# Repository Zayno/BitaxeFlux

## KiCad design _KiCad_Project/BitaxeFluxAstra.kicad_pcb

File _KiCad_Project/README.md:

# BitaxeFluxAstra A1 — Clean Engineering Project

Open `BitaxeFluxAstra.kicad_pro` in **KiCad 10**. All five editable sheets, the preserved board and all used symbol/footprint libraries are included.

This package is for **pre-layout engineering review**. The PCB remains the earlier snapshot; it does not implement all A1 schematic changes. Do not manufacture this board from this package or automatically update it from the schematic as part of cleanup.

The ASIC is **Bitmain BM1373**, reference **A1**, configuration **Mode 1**. Its local symbol is `BitaxeFluxAstra:BM1373_mode1` and its footprint is `BitaxeFluxAstra:BM1373`.

R49 remains DNP. Unqualified thermal-shutdown and optional programming/tuning parts retain their DNP states. Qualification HOLD items remain open.

Read `PROJECT_CLEANUP_REPORT.md` for verification, preserved HOLD items and limitations. Exact historical file/migration names are isolated in `engineering_reference_notes.md`. `BitaxeFluxAstra_Integrity.json` records current structural verification. `SHA256SUMS.txt` covers delivery files except itself.

Static equivalence and extracted-package dependency checks passed. **Native KiCad opening, ERC, DRC and exported-netlist comparison have not been run** in this environment. Full acceptance remains pending that review. Optional standard 3D models use the normal KiCad 10 3D-model package; every required custom model is local or embedded.

No placement, routing or fabrication outputs are included. The supplied licence is preserved in `LICENSE`.

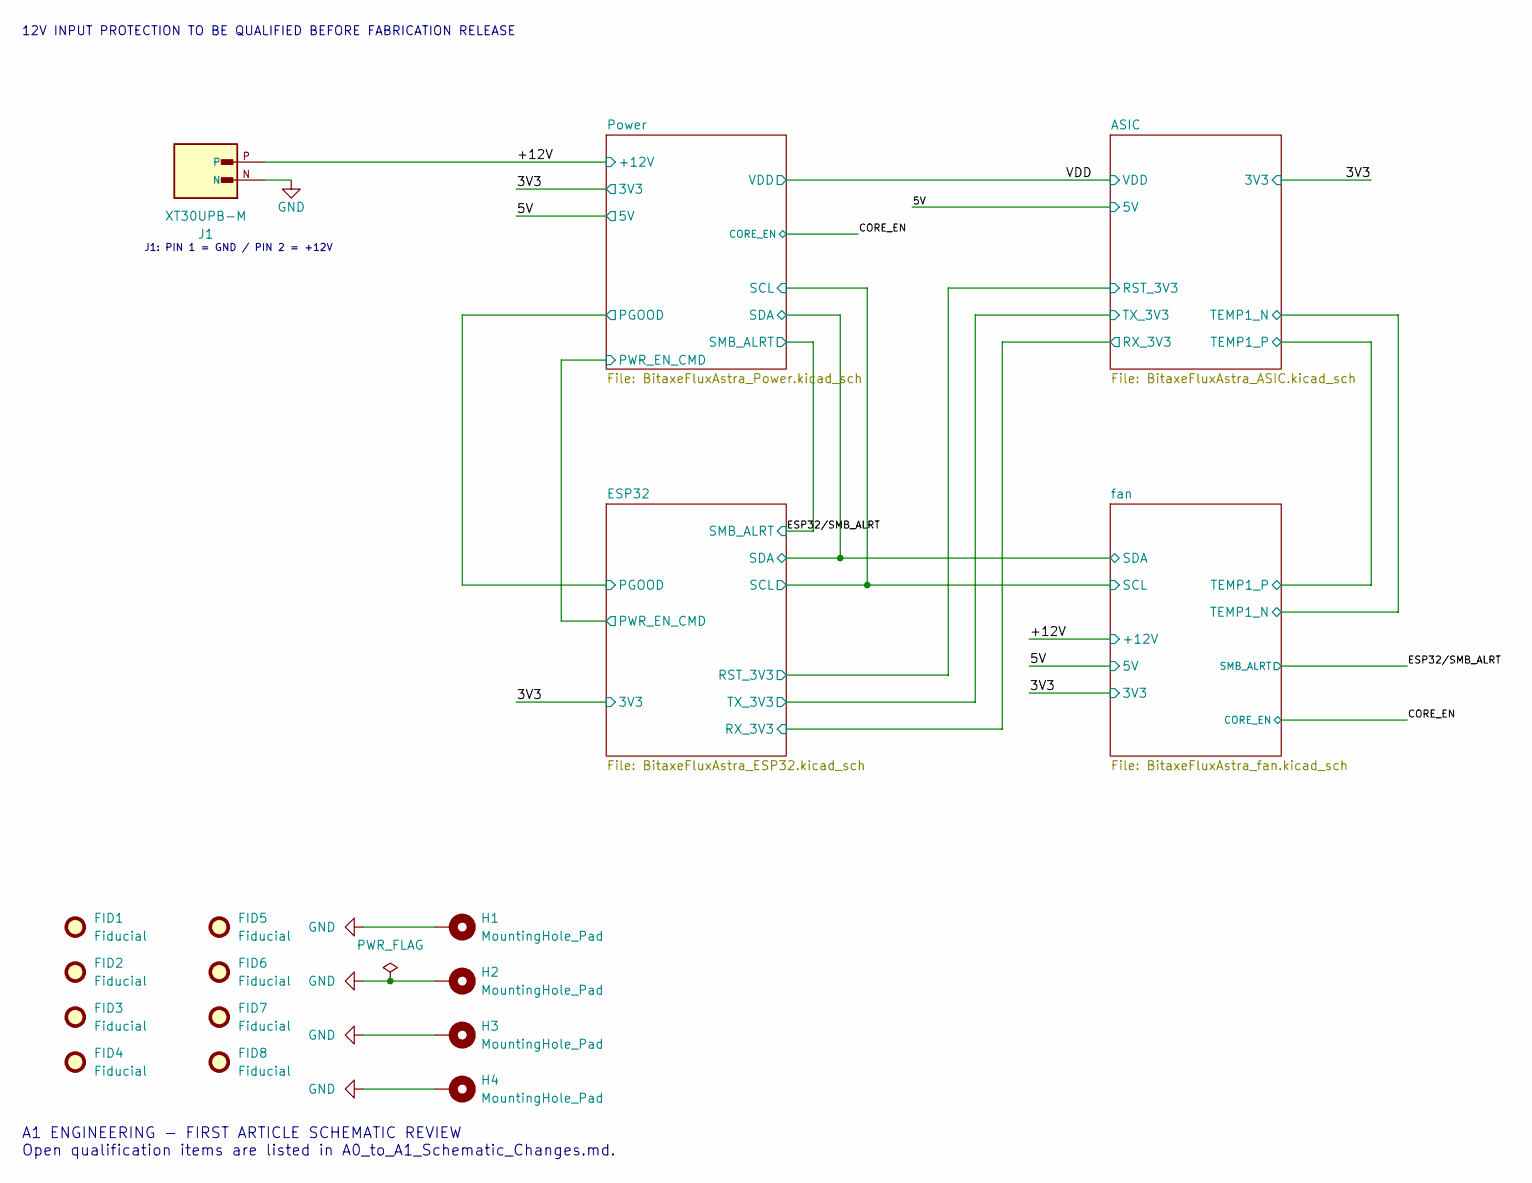
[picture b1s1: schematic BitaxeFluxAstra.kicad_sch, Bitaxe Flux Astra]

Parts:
FID1, FID2, FID3, FID4, FID5, FID6, FID7, FID8: Fiducial; Fiducial_1mm_Mask2mm
H1, H2, H3, H4: MountingHole_Pad; MountingHole_3.2mm_M3_Pad_Via
J1: XT30UPB-M; AMASS_XT30UPB-M

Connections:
+12V: J1.P; also elsewhere on the board
GND: H1.1 (1_1), H2.1 (1_1), H3.1 (1_1), H4.1 (1_1), J1.N; also elsewhere on the board

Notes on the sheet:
J1: PIN 1 = GND / PIN 2 = +12V
A1 ENGINEERING - FIRST ARTICLE SCHEMATIC REVIEW Open qualification items are listed in A0_to_A1_Schematic_Changes.md.
12V INPUT PROTECTION TO BE QUALIFIED BEFORE FABRICATION RELEASE

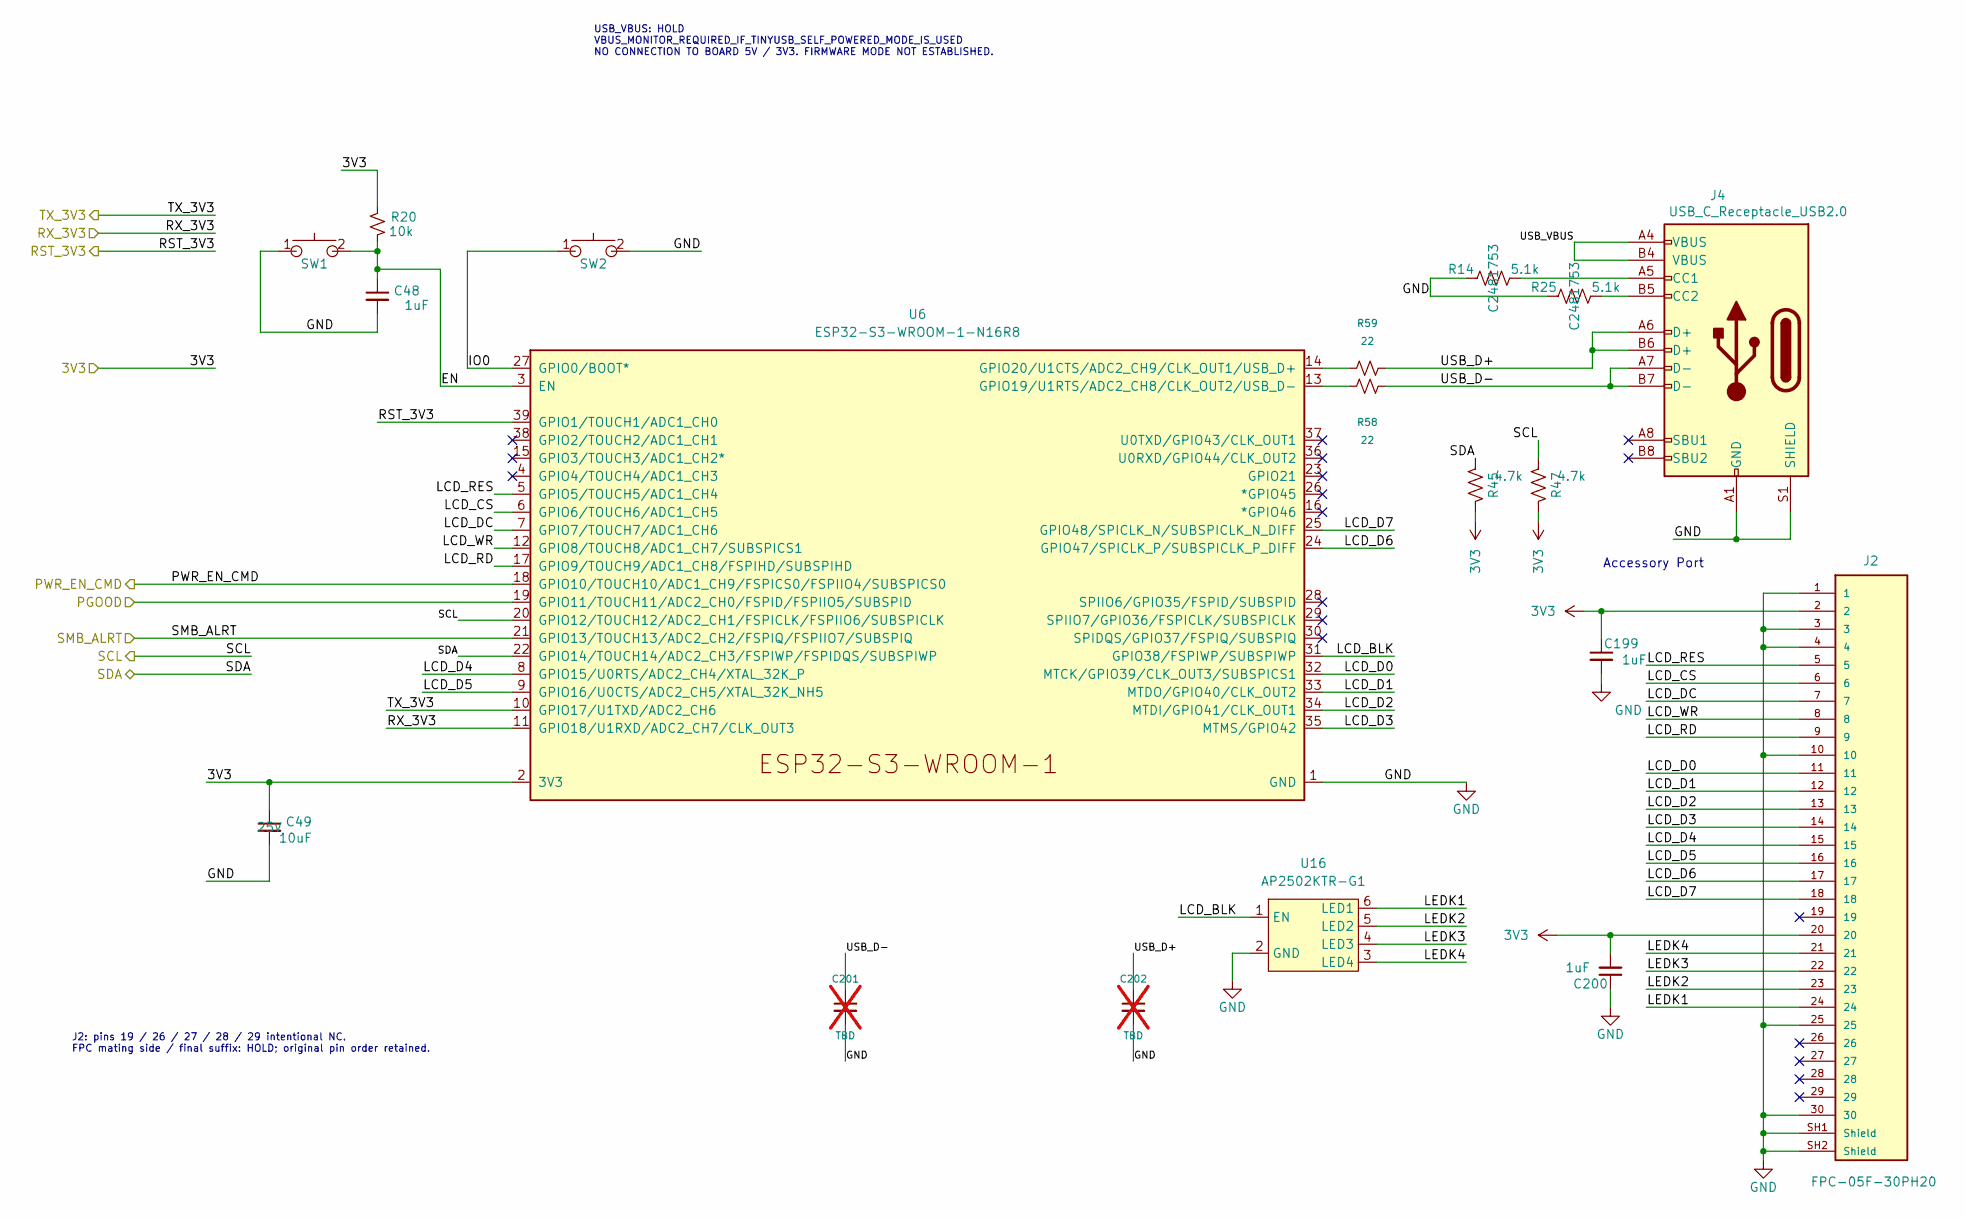
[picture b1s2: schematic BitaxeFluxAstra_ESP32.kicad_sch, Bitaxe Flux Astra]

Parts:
C48, C199, C200: 1uF; C_0603_1608Metric; PARTNO TMK107B7105KA-T
C49: 10uF; C_0603_1608Metric; Voltage 25V; PARTNO GRM188R61E106KA73D; LCSC C344022
C201, C202: TBD; C_0402_1005Metric; PARTNO TBD / QUALIFY; not fitted
J2: FPC-05F-30PH20; FPC-SMD_30P-P0.50_XUNPU_FPC-05F-30PH20; PARTNO FPC-05FB-30PH20
J4: USB_C_Receptacle_USB2.0; USB_C_Receptacle_GCT_USB4105-xx-A; PARTNO USB4105-GF-A
R14, R25: 5.1k; R_0402_1005Metric; PARTNO RMCF0402JT5K10; LCSC C2481753
R20: 10k; R_0402_1005Metric; PARTNO RC0402JR-0710KL; LCSC C25744
R45, R47: 4.7k; R_0402_1005Metric; PARTNO RC0402DR-074K7L; LCSC C471788
R58, R59: 22; R_0402_1005Metric; PARTNO RC0402FR-0722RL
SW1, SW2: SW_Push_SPST_NO; SW_CS1213AGF260_CRS; PARTNO CS1213AGF260
U6: ESP32-S3-WROOM-1-N16R8; ESP32-S3-WROOM-1; PARTNO ESP32-S3-WROOM-1-N16R8
U16: AP2502KTR-G1; SOT-23-6; PARTNO AP2502KTR-G1

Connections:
3V3: C49.1, C199.1, C200.2, J2.2, J2.20, R20.2, R45.1, R47.1, U6.2 (3V3); also elsewhere on the board
/ASIC/RST_3V3: U6.39 (GPIO1/TOUCH1/ADC1_CH0); also elsewhere on the board
/ASIC/RX_3V3: U6.11 (GPIO18/U1RXD/ADC2_CH7/CLK_OUT3); also elsewhere on the board
/ASIC/TX_3V3: U6.10 (GPIO17/U1TXD/ADC2_CH6); also elsewhere on the board
/ESP32/EN: C48.1, R20.1, SW1.2, U6.3 (EN)
/ESP32/IO0: SW2.1, U6.27 (GPIO0/BOOT*)
/ESP32/LCD_BLK: U6.31 (GPIO38/FSPIWP/SUBSPIWP), U16.1 (EN)
/ESP32/LCD_CS: J2.6, U6.6 (GPIO6/TOUCH6/ADC1_CH5)
/ESP32/LCD_D0: J2.11, U6.32 (MTCK/GPIO39/CLK_OUT3/SUBSPICS1)
/ESP32/LCD_D1: J2.12, U6.33 (MTDO/GPIO40/CLK_OUT2)
/ESP32/LCD_D2: J2.13, U6.34 (MTDI/GPIO41/CLK_OUT1)
/ESP32/LCD_D3: J2.14, U6.35 (MTMS/GPIO42)
/ESP32/LCD_D4: J2.15, U6.8 (GPIO15/U0RTS/ADC2_CH4/XTAL_32K_P)
/ESP32/LCD_D5: J2.16, U6.9 (GPIO16/U0CTS/ADC2_CH5/XTAL_32K_NH5)
/ESP32/LCD_D6: J2.17, U6.24 (GPIO47/SPICLK_P/SUBSPICLK_P_DIFF)
/ESP32/LCD_D7: J2.18, U6.25 (GPIO48/SPICLK_N/SUBSPICLK_N_DIFF)
/ESP32/LCD_DC: J2.7, U6.7 (GPIO7/TOUCH7/ADC1_CH6)
/ESP32/LCD_RD: J2.9, U6.17 (GPIO9/TOUCH9/ADC1_CH8/FSPIHD/SUBSPIHD)
/ESP32/LCD_RES: J2.5, U6.5 (GPIO5/TOUCH5/ADC1_CH4)
/ESP32/LCD_WR: J2.8, U6.12 (GPIO8/TOUCH8/ADC1_CH7/SUBSPICS1)
/ESP32/LEDK1: J2.24, U16.6 (LED1)
/ESP32/LEDK2: J2.23, U16.5 (LED2)
/ESP32/LEDK3: J2.22, U16.4 (LED3)
/ESP32/LEDK4: J2.21, U16.3 (LED4)
/ESP32/PWR_EN_CMD: U6.18 (GPIO10/TOUCH10/ADC1_CH9/FSPICS0/FSPIIO4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); also elsewhere on the board
/ESP32/SCL: R47.2, U6.20 (GPIO12/TOUCH12/ADC2_CH1/FSPICLK/FSPIIO6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); also elsewhere on the board
/ESP32/SDA: R45.2, U6.22 (GPIO14/TOUCH14/ADC2_CH3/FSPIWP/FSPIDQS/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); also elsewhere on the board
/ESP32/USB_D+: C202.1, J4.A6 (D+), J4.B6 (D+), R59.2
/ESP32/USB_D-: C201.1, J4.A7 (D-), J4.B7 (D-), R58.2
/ESP32/USB_VBUS: J4.A4 (VBUS), J4.B4 (VBUS)
/ESP32/SMB_ALRT: U6.21 (GPIO13/TOUCH13/ADC2_CH2/FSPIQ/FSPIIO7/S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); also elsewhere on the board
/Power/PGOOD: U6.19 (GPIO11/TOUCH11/ADC2_CH0/FSPID/FSPIIO5/S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); also elsewhere on the board
GND: C48.2, C49.2, C199.2, C200.1, C201.2, C202.2, J2.1, J2.3, J2.4, J2.10, J2.25, J2.30, J2.SH1 (Shield), J2.SH2 (Shield), J4.A1 (GND), J4.B1 (GND), J4.S1 (SHIELD), R14.1, R25.1, SW1.1, SW2.2, U6.1 (GND), U6.40 (GND), U6.41 (GND), U16.2 (GND); also elsewhere on the board
unnamed: J4.A5 (CC1), R14.2
unnamed: J4.B5 (CC2), R25.2
unnamed: R58.1, U6.13 (GPIO19/U1RTS/ADC2_CH8/CLK_OUT2/USB_D-)
unnamed: R59.1, U6.14 (GPIO20/U1CTS/ADC2_CH9/CLK_OUT1/USB_D+)

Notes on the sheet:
J2: pins 19 / 26 / 27 / 28 / 29 intentional NC. FPC mating side / final suffix: HOLD; original pin order retained.
USB_VBUS: HOLD VBUS_MONITOR_REQUIRED_IF_TINYUSB_SELF_POWERED_MODE_IS_USED NO CONNECTION TO BOARD 5V / 3V3. FIRMWARE MODE NOT ESTABLISHED.
Accessory Port

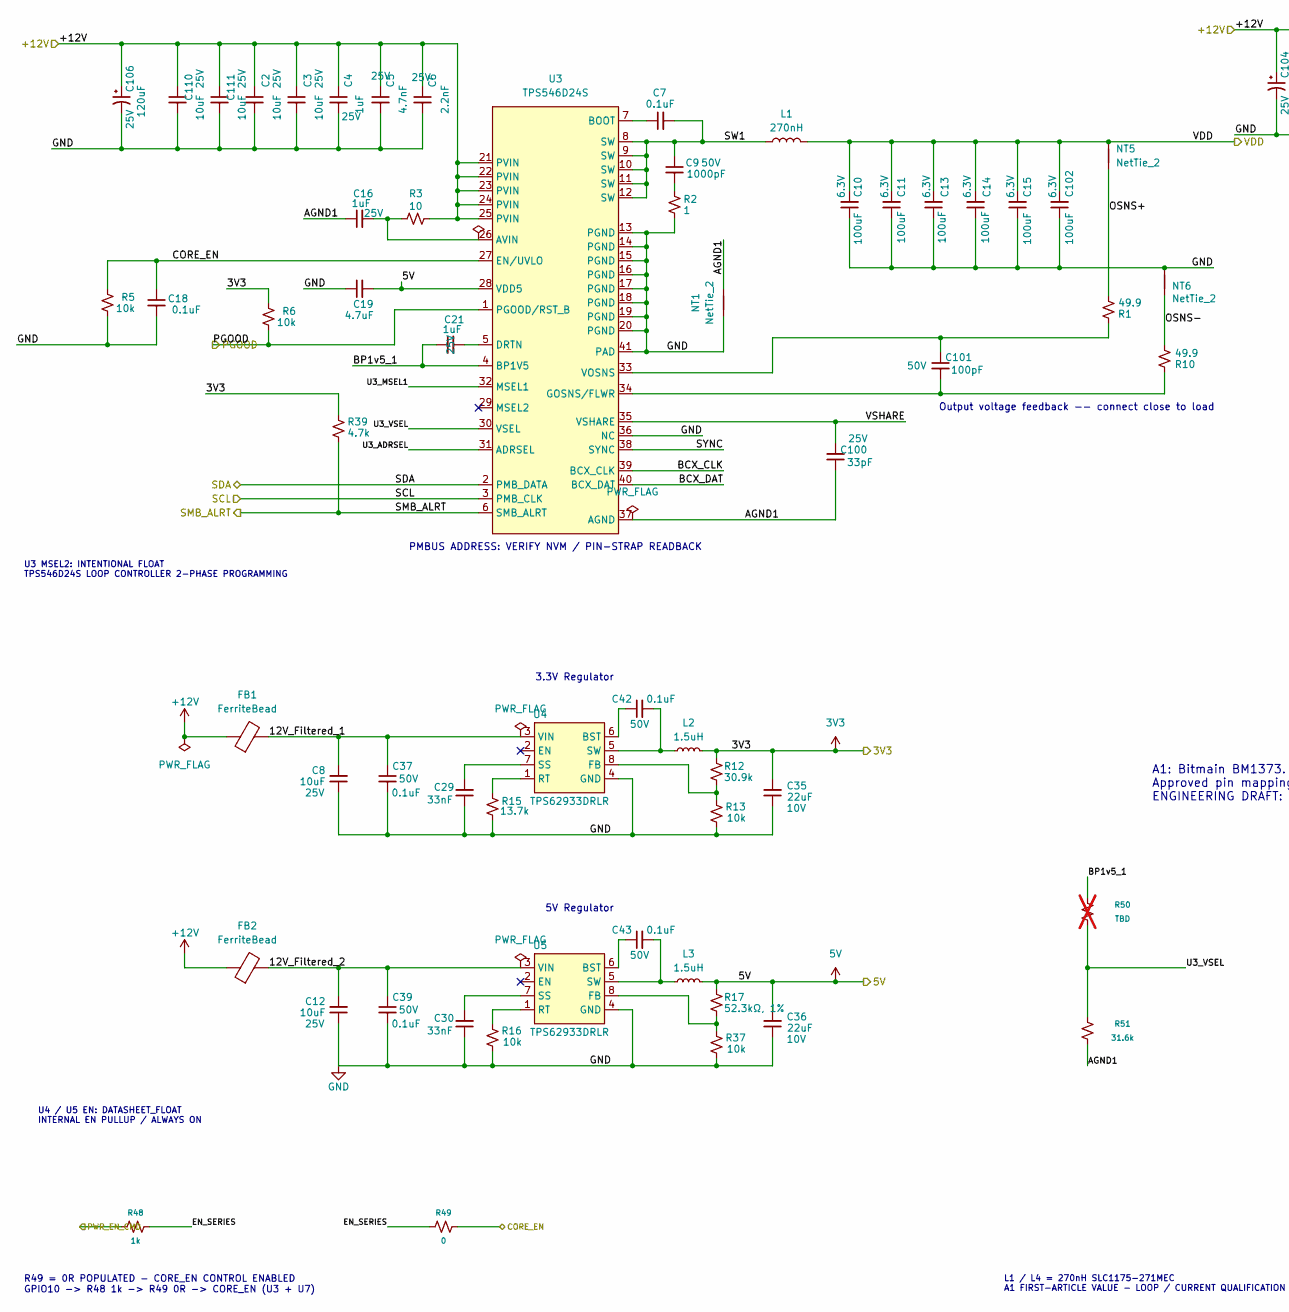
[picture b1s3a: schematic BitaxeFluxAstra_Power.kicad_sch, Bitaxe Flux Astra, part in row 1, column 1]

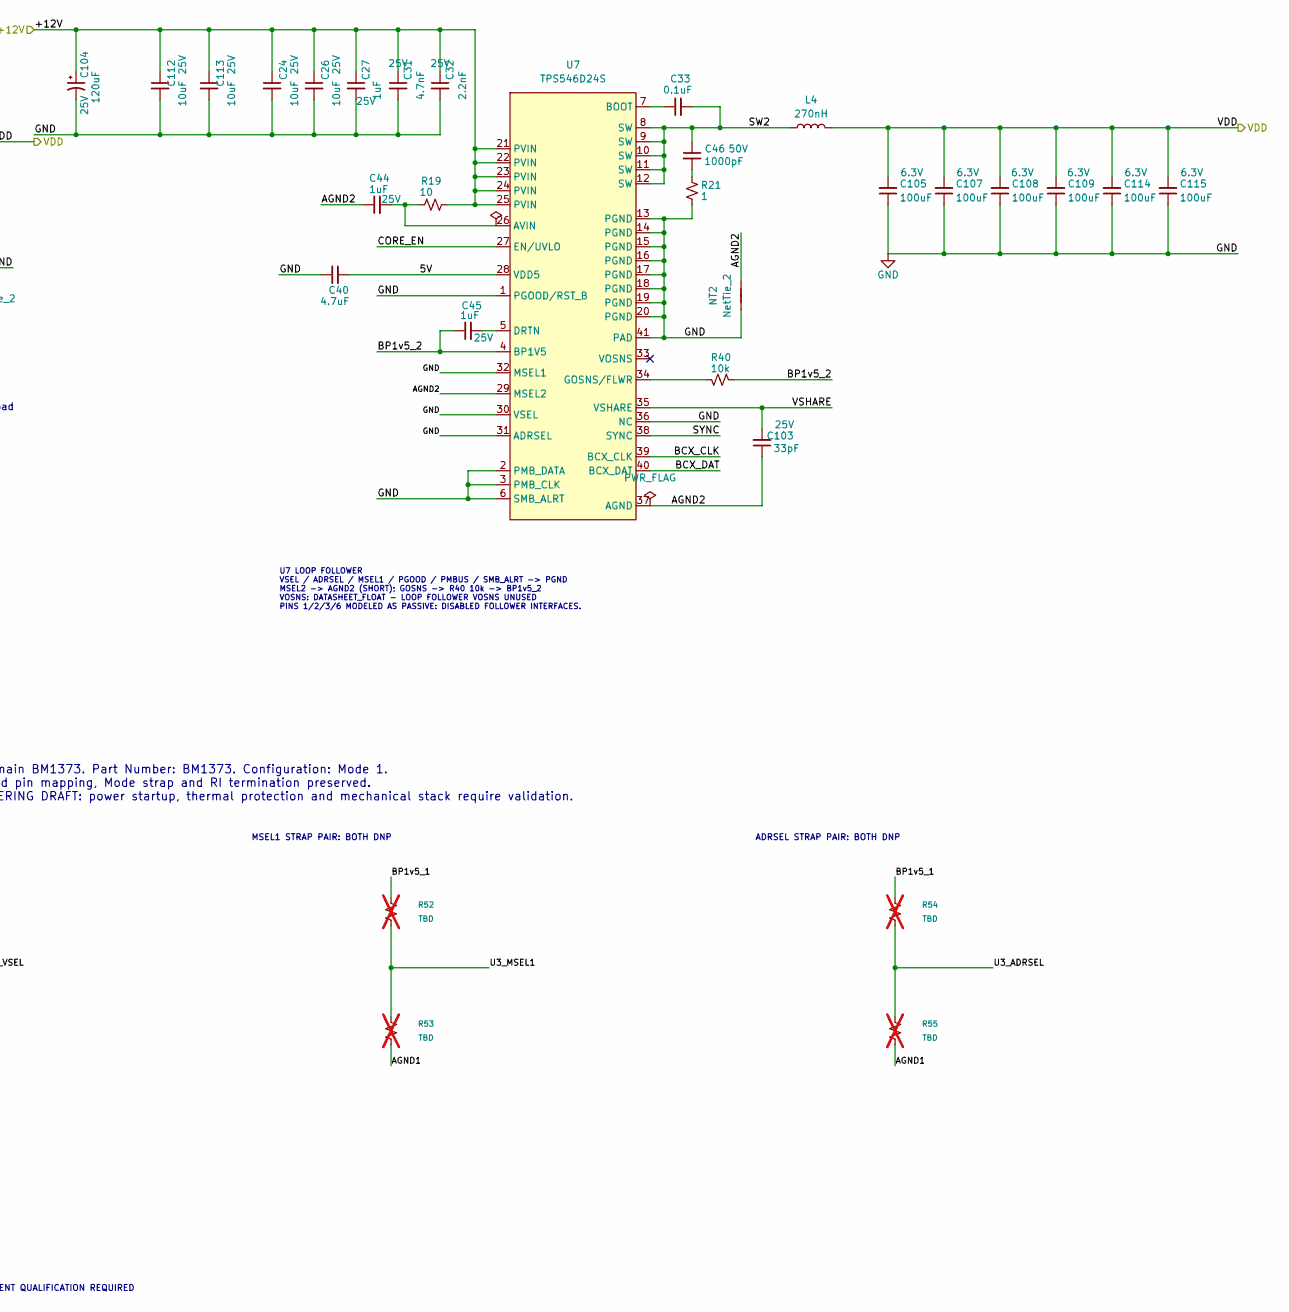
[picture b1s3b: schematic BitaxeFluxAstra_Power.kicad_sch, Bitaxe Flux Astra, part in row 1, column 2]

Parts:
C2, C3, C24, C26, C110, C111, C112, C113: 10uF; C_0603_1608Metric; Voltage 25V; PARTNO GRM188R61E106KA73D
C4, C16, C21, C27, C44, C45: 1uF; C_0603_1608Metric; Voltage 25V; PARTNO TMK107B7105KA-T
C5, C31: 4.7nF; C_0402_1005Metric; Voltage 25V; PARTNO GRM155R71E472KA01D
C6, C32: 2.2nF; C_0402_1005Metric; Voltage 25V; PARTNO GRM155R61H222KA01D
C7, C18, C33: 0.1uF; C_0402_1005Metric; PARTNO KGM05AR71C104KH
C8, C12: 10uF; C_0603_1608Metric; Voltage 25V; PARTNO GRM188R61E106KA73D; LCSC C344022
C9, C46: 1000pF; C_0805_2012Metric; Voltage 50V; PARTNO CC0805KRX7R9BB102
C10, C11, C13, C14, C15, C102, C105, C107, C108, C109, C114, C115: 100uF; C_1206_3216Metric; Voltage 6.3V; PARTNO CL31A107MQHNNNE
C19, C40: 4.7uF; C_0402_1005Metric; PARTNO GRM155R61A475MEAAD
C29, C30: 33nF; C_0402_1005Metric; PARTNO CC0402KRX7R9BB333; LCSC C106862
C35, C36: 22uF; C_0805_2012Metric; Voltage 10V; PARTNO CL21A226MPQNNNE; LCSC C29277
C37, C39, C42, C43: 0.1uF; C_0402_1005Metric; Voltage 50V; PARTNO GRM155R71H104KE14D; LCSC C77020
C100, C103: 33pF; C_0402_1005Metric; Voltage 25V; PARTNO KGM05ACG1E330JH
C101: 100pF; C_0402_1005Metric; Voltage 50V; PARTNO CC0402JRNPO9BN101
C104, C106: 120uF; CP_Elec_6.3x5.9; Voltage 25V; PARTNO TBD / QUALIFY
FB1, FB2: FerriteBead; C_1206_3216Metric; PARTNO BLM31KN601SN1L
L1, L4: 270nH; SLC1175-271MEC_COC; PARTNO SLC1175-271MEC
L2, L3: 1.5uH; IND-SMD_L2.0-W1.6; PARTNO FTC201612S1R5MBCA; LCSC C5832350
NT1, NT2, NT5, NT6: NetTie_2; NetTie-2_SMD_Pad0.2mmx1mm
R1, R10: 49.9; R_0402_1005Metric; PARTNO RC0402FR-0749R9L
R2, R21: 1; R_0805_2012Metric; PARTNO ESR10EZPJ1R0
R3, R19: 10; R_0402_1005Metric; PARTNO RC0402FR-0710RL
R5, R6, R40: 10k; R_0402_1005Metric; PARTNO RC0402JR-0710KL
R12: 30.9k; R_0402_1005Metric; PARTNO RC0402FR-0730K9L; LCSC C185428
R13, R16: 10k; R_0402_1005Metric; PARTNO RC0402JR-0710KL; LCSC C25744
R15: 13.7k; R_0402_1005Metric; PARTNO RC0402FR-0713K7L; LCSC C274888
R17: 52.3kΩ, 1%; R_0402_1005Metric
R37: 10k; R_0402_1005Metric
R39: 4.7k; R_0402_1005Metric; PARTNO RC0402JR-074K7L
R48: 1k; R_0402_1005Metric; PARTNO RC0402FR-071KL
R49: 0; R_0402_1005Metric; PARTNO Yageo RC0402JR-070RL
R50, R52, R53, R54, R55: TBD; R_0402_1005Metric; PARTNO TBD / QUALIFY; not fitted
R51: 31.6k; R_0402_1005Metric
U3, U7: TPS546D24S; LQFN40-CLIP; PARTNO TPS546D24SRVFR
U4, U5: TPS62933DRLR; SOT-583-8_L2.1-W1.2-P0.50-LS1.6-BR; PARTNO TPS62933DRLR; LCSC C3200405

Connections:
3V3: C35.2, L2.2, R6.2, R12.2, R39.1; also elsewhere on the board
+12V: C2.1, C3.1, C4.1, C5.1, C6.1, C24.1, C26.1, C27.1, C31.1, C32.1, C104.1, C106.1, C110.1, C111.1, C112.1, C113.1, FB1.1, FB2.1, R3.1, R19.1, U3.21 (PVIN), U3.22 (PVIN), U3.23 (PVIN), U3.24 (PVIN), U3.25 (PVIN), U7.21 (PVIN), U7.22 (PVIN), U7.23 (PVIN), U7.24 (PVIN), U7.25 (PVIN); also elsewhere on the board
/5V: C19.2, C36.2, C40.2, L3.2, R17.2, U3.28 (VDD5), U7.28 (VDD5); also elsewhere on the board
/CORE_EN: C18.1, R5.2, R49.2, U3.27 (EN/UVLO), U7.27 (EN/UVLO); also elsewhere on the board
/ESP32/PWR_EN_CMD: R48.1; also elsewhere on the board
/ESP32/SCL: U3.3 (PMB_CLK); also elsewhere on the board
/ESP32/SDA: U3.2 (PMB_DATA); also elsewhere on the board
/ESP32/SMB_ALRT: R39.2, U3.6 (SMB_ALRT); also elsewhere on the board
/Power/12V_Filtered_1: C8.2, C37.1, FB1.2, U4.3 (VIN)
/Power/12V_Filtered_2: C12.2, C39.1, FB2.2, U5.3 (VIN)
/Power/AGND1: C16.1, C100.1, NT1.2, R51.2, R53.2, R55.2, U3.37 (AGND)
/Power/AGND2: C44.1, C103.1, NT2.2, U7.29 (MSEL2), U7.37 (AGND)
/Power/BCX_CLK: U3.39 (BCX_CLK), U7.39 (BCX_CLK)
/Power/BCX_DAT: U3.40 (BCX_DAT), U7.40 (BCX_DAT)
/Power/BP1v5_1: C21.1, R50.1, R52.1, R54.1, U3.4 (BP1V5)
/Power/BP1v5_2: C45.1, R40.1, U7.4 (BP1V5)
/Power/EN_SERIES: R48.2, R49.1
/Power/OSNS+: NT5.1, R1.2
/Power/OSNS-: NT6.1, R10.1
/Power/PGOOD: R6.1, U3.1 (PGOOD/RST_B); also elsewhere on the board
/Power/SW1: C7.2, C9.1, L1.1, U3.8 (SW), U3.9 (SW), U3.10 (SW), U3.11 (SW), U3.12 (SW)
/Power/SW2: C33.2, C46.1, L4.1, U7.8 (SW), U7.9 (SW), U7.10 (SW), U7.11 (SW), U7.12 (SW)
/Power/SYNC: U3.38 (SYNC), U7.38 (SYNC)
/Power/U3_ADRSEL: R54.2, R55.1, U3.31 (ADRSEL)
/Power/U3_MSEL1: R52.2, R53.1, U3.32 (MSEL1)
/Power/U3_VSEL: R50.2, R51.1, U3.30 (VSEL)
/Power/VSHARE: C100.2, C103.2, U3.35 (VSHARE), U7.35 (VSHARE)
/VDD: C10.2, C11.2, C13.2, C14.2, C15.2, C102.2, C105.2, C107.2, C108.2, C109.2, C114.2, C115.2, L1.2, L4.2, NT5.2; also elsewhere on the board
GND: C2.2, C3.2, C4.2, C5.2, C6.2, C8.1, C10.1, C11.1, C12.1, C13.1, C14.1, C15.1, C18.2, C19.1, C24.2, C26.2, C27.2, C29.1, C30.1, C31.2, C32.2, C35.1, C36.1, C37.2, C39.2, C40.1, C102.1, C104.2, C105.1, C106.2, C107.1, C108.1, C109.1, C110.2, C111.2, C112.2, C113.2, C114.1, C115.1, NT1.1, NT2.1, NT6.2, R2.2, R5.1, R13.1, R15.1, R16.1, R21.2, R37.1, U3.13 (PGND), U3.14 (PGND), U3.15 (PGND), U3.16 (PGND), U3.17 (PGND), U3.18 (PGND), U3.19 (PGND), U3.20 (PGND), U3.36 (NC), U3.41 (PAD), U4.4 (GND), U5.4 (GND), U7.1 (PGOOD/RST_B), U7.2 (PMB_DATA), U7.3 (PMB_CLK), U7.6 (SMB_ALRT), U7.13 (PGND), U7.14 (PGND), U7.15 (PGND), U7.16 (PGND), U7.17 (PGND), U7.18 (PGND), U7.19 (PGND), U7.20 (PGND), U7.30 (VSEL), U7.31 (ADRSEL), U7.32 (MSEL1), U7.36 (NC), U7.41 (PAD); also elsewhere on the board
unnamed: C9.2, R2.1
unnamed: C46.2, R21.1
unnamed: C16.2, R3.2, U3.26 (AVIN)
unnamed: C7.1, U3.7 (BOOT)
unnamed: C21.2, U3.5 (DRTN)
unnamed: C101.2, R10.2, U3.34 (GOSNS/FLWR)
unnamed: C101.1, R1.1, U3.33 (VOSNS)
unnamed: C42.1, U4.6 (BST)
unnamed: R12.1, R13.2, U4.8 (FB)
unnamed: R15.2, U4.1 (RT)
unnamed: C29.2, U4.7 (SS)
unnamed: C42.2, L2.1, U4.5 (SW)
unnamed: C43.1, U5.6 (BST)
unnamed: R17.1, R37.2, U5.8 (FB)
unnamed: R16.2, U5.1 (RT)
unnamed: C30.2, U5.7 (SS)
unnamed: C43.2, L3.1, U5.5 (SW)
unnamed: C44.2, R19.2, U7.26 (AVIN)
unnamed: C33.1, U7.7 (BOOT)
unnamed: C45.2, U7.5 (DRTN)
unnamed: R40.2, U7.34 (GOSNS/FLWR)

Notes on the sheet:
ADRSEL STRAP PAIR: BOTH DNP
Output voltage feedback -- connect close to load
L1 / L4 = 270nH SLC1175-271MEC A1 FIRST-ARTICLE VALUE - LOOP / CURRENT QUALIFICATION REQUIRED
MSEL1 STRAP PAIR: BOTH DNP
A1: Bitmain BM1373. Part Number: BM1373. Configuration: Mode 1. Approved pin mapping, Mode strap and RI termination preserved. ENGINEERING DRAFT: power startup, thermal protection and mechanical stack require validation.
R49 = 0R POPULATED - CORE_EN CONTROL ENABLED GPIO10 -> R48 1k -> R49 0R -> CORE_EN (U3 + U7)
U7 LOOP FOLLOWER VSEL / ADRSEL / MSEL1 / PGOOD / PMBUS / SMB_ALRT -> PGND MSEL2 -> AGND2 (SHORT); GOSNS -> R40 10k -> BP1v5_2 VOSNS: DATASHEET_FLOAT - LOOP FOLLOWER VOSNS UNUSED PINS 1/2/3/6 MODELED AS PASSIVE: DISABLED FOLLOWER INTERFACES.
U4 / U5 EN: DATASHEET_FLOAT INTERNAL EN PULLUP / ALWAYS ON
PMBUS ADDRESS: VERIFY NVM / PIN-STRAP READBACK
5V Regulator
U3 MSEL2: INTENTIONAL FLOAT TPS546D24S LOOP CONTROLLER 2-PHASE PROGRAMMING
3.3V Regulator

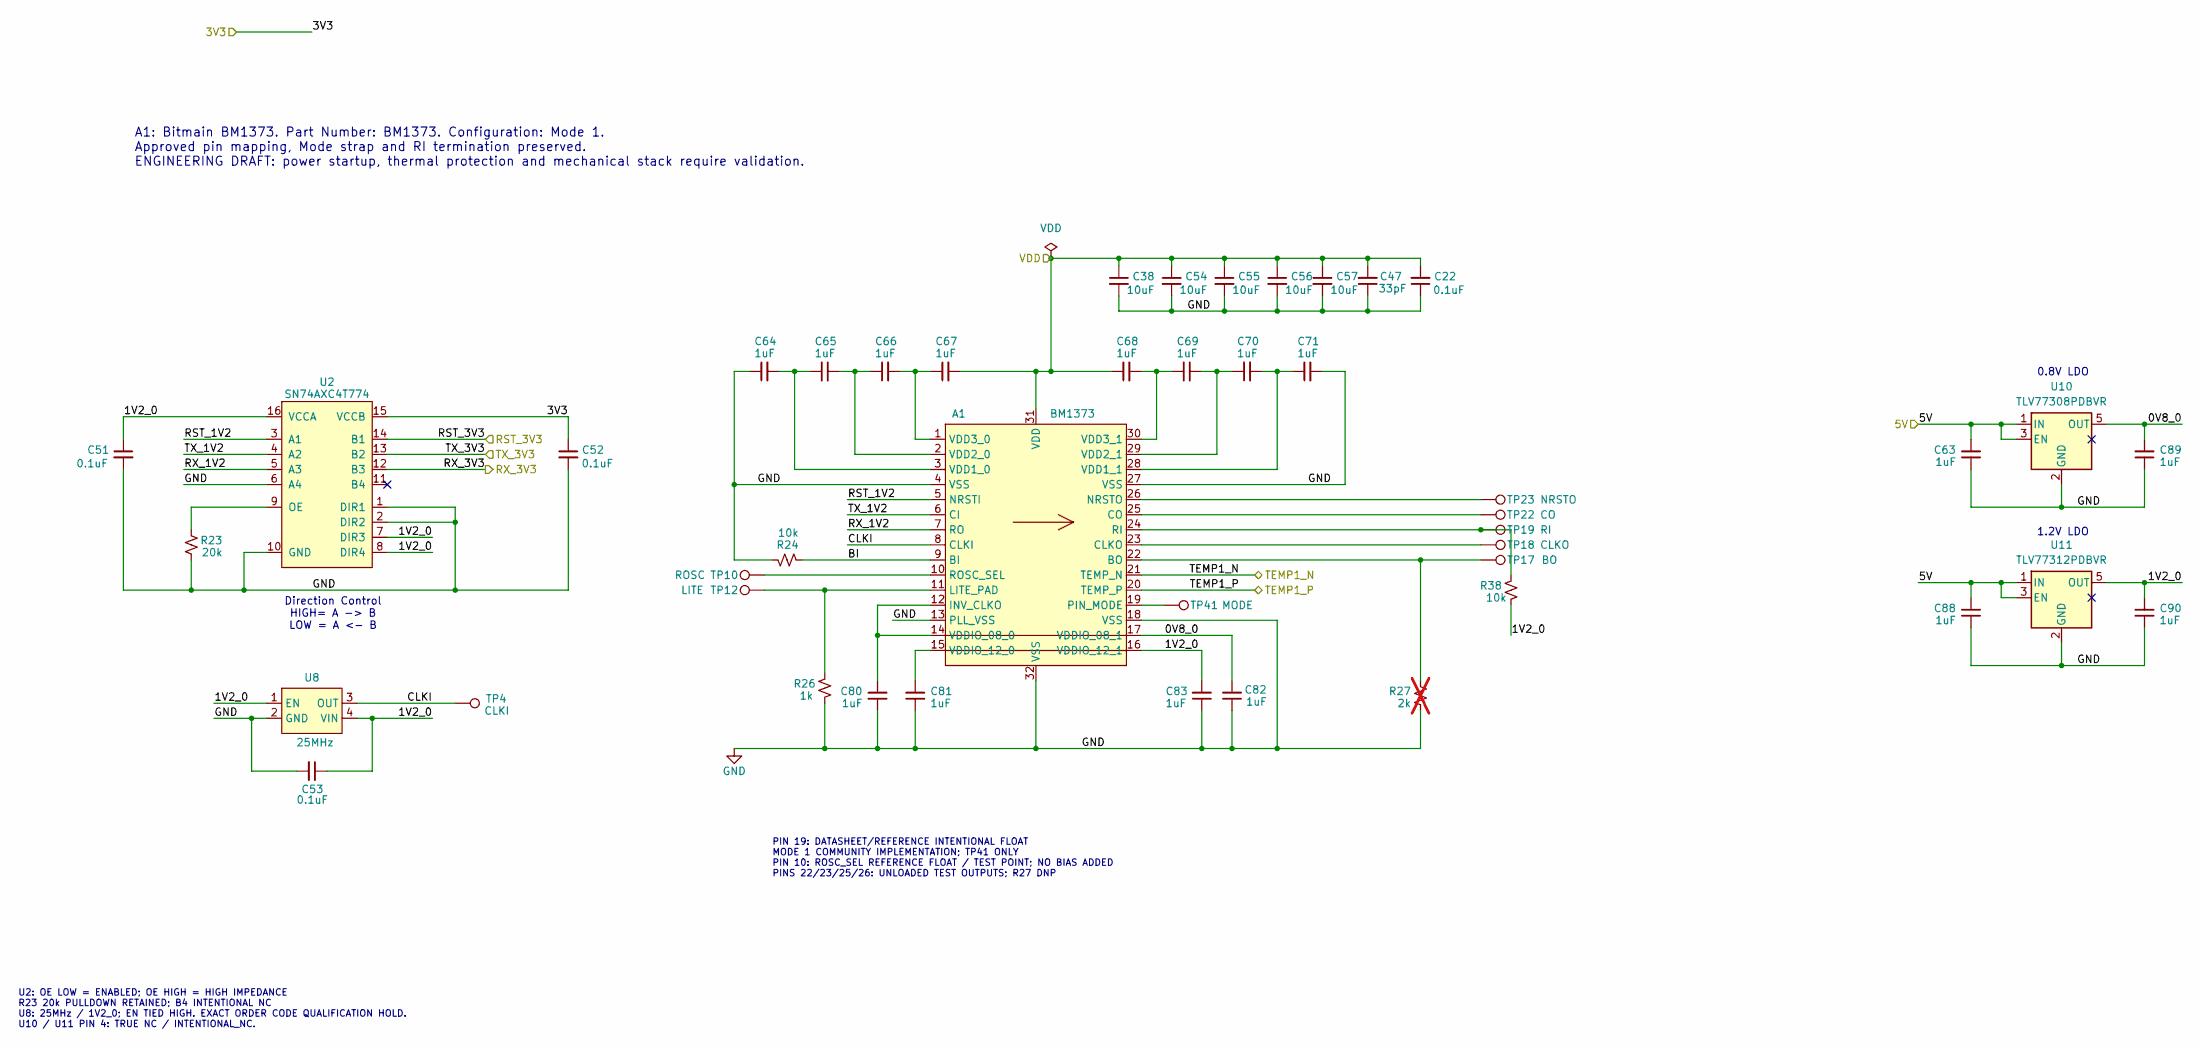
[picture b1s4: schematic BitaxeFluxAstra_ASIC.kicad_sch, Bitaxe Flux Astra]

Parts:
A1: BM1373; PARTNO BM1373
C22: 0.1uF; C_0402_1005Metric; PARTNO GRM155R71H104KE14D; LCSC C77020
C38, C54, C55, C56, C57: 10uF; C_0603_1608Metric; Voltage 25V; PARTNO GRM188R61E106KA73D; LCSC C344022
C47: 33pF; C_0402_1005Metric; Voltage 25V; PARTNO KGM05ACG1E330JH
C51, C52, C53: 0.1uF; C_0402_1005Metric; PARTNO KGM05AR71C104KH
C63, C64, C65, C66, C67, C68, C69, C70, C71, C80, C81, C82, C83, C88, C89, C90: 1uF; C_0402_1005Metric; PARTNO EMK105BJ105MV-F; LCSC C2177690
R23: 20k; R_0402_1005Metric; PARTNO RC0402FR-0720KL
R24: 10k; R_0402_1005Metric; PARTNO RC0402JR-0710KL; LCSC C25744
R26: 1k; R_0402_1005Metric; PARTNO RC0402FR-071KL
R27: 2k; R_0402_1005Metric; PARTNO RT0402BRD072KL; not fitted
R38: 10k; R_0402_1005Metric; PARTNO RC0402JR-0710KL
TP4: CLKI; TestPoint_Pad_D1.0mm
TP10: ROSC; TestPoint_Pad_1.0x0.4mm
TP12: LITE; TestPoint_Pad_1.0x0.4mm
TP17: BO; TestPoint_Pad_1.0x0.4mm
TP18: CLKO; TestPoint_Pad_1.0x0.4mm
TP19: RI; TestPoint_Pad_1.0x0.4mm
TP22: CO; TestPoint_Pad_1.0x0.4mm
TP23: NRSTO; TestPoint_Pad_1.0x0.4mm
TP41: MODE; TestPoint_Pad_1.0x0.4mm
U2: SN74AXC4T774; TSSOP-16_4.4x5mm_P0.65mm; PARTNO SN74AXC4T774PWR; LCSC C1849453
U8: 25MHz; SMD3225-4P; PARTNO SX3M25.000E20F30THN; LCSC C5137262
U10: TLV77308PDBVR; SOT-23-5; PARTNO TLV77308PDBVR
U11: TLV77312PDBVR; SOT-23-5; PARTNO TLV77312PDBVR

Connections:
3V3: C52.1, U2.15 (VCCB); also elsewhere on the board
/5V: C63.2, C88.2, U10.1 (IN), U10.3 (EN), U11.1 (IN), U11.3 (EN); also elsewhere on the board
/ASIC/BI: A1.9 (BI), R24.2
/ASIC/CLKI: A1.8 (CLKI), TP4.1 (1_1), U8.3 (OUT)
/ASIC/RST_1V2: A1.5 (NRSTI), U2.3 (A1)
/ASIC/RST_3V3: U2.14 (B1); also elsewhere on the board
/ASIC/RX_1V2: A1.7 (RO), U2.5 (A3)
/ASIC/RX_3V3: U2.12 (B3); also elsewhere on the board
/ASIC/TEMP1_N: A1.21 (TEMP_N); also elsewhere on the board
/ASIC/TEMP1_P: A1.20 (TEMP_P); also elsewhere on the board
/ASIC/TX_1V2: A1.6 (CI), U2.4 (A2)
/ASIC/TX_3V3: U2.13 (B2); also elsewhere on the board
/VDD: A1.31 (VDD), C22.2, C38.1, C47.2, C54.1, C55.1, C56.1, C57.1, C67.2, C68.1; also elsewhere on the board
GND: A1.4 (VSS), A1.13 (PLL_VSS), A1.18 (VSS), A1.27 (VSS), A1.32 (VSS), C22.1, C38.2, C47.1, C51.2, C52.2, C53.2, C54.2, C55.2, C56.2, C57.2, C63.1, C64.1, C71.2, C80.1, C81.1, C82.1, C83.1, C88.1, C89.1, C90.1, R23.1, R24.1, R26.1, R27.1, U2.1 (DIR1), U2.2 (DIR2), U2.6 (A4), U2.10 (GND), U8.2 (GND), U10.2 (GND), U11.2 (GND); also elsewhere on the board
unnamed: A1.22 (BO), R27.2, TP17.1 (1_1)
unnamed: A1.23 (CLKO), TP18.1 (1_1)
unnamed: A1.25 (CO), TP22.1 (1_1)
unnamed: A1.11 (LITE_PAD), R26.2, TP12.1 (1_1)
unnamed: A1.26 (NRSTO), TP23.1 (1_1)
unnamed: A1.19 (PIN_MODE), TP41.1 (1_1)
unnamed: A1.24 (RI), R38.2, TP19.1 (1_1)
unnamed: A1.10 (ROSC_SEL), TP10.1 (1_1)
unnamed: A1.3 (VDD1_0), C64.2, C65.1
unnamed: A1.28 (VDD1_1), C70.2, C71.1
unnamed: A1.2 (VDD2_0), C65.2, C66.1
unnamed: A1.29 (VDD2_1), C69.2, C70.1
unnamed: A1.1 (VDD3_0), C66.2, C67.1
unnamed: A1.30 (VDD3_1), C68.2, C69.1
unnamed: R23.2, U2.9 (OE)

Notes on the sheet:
1.2V LDO
U2: OE LOW = ENABLED; OE HIGH = HIGH IMPEDANCE R23 20k PULLDOWN RETAINED; B4 INTENTIONAL NC U8: 25MHz / 1V2_0; EN TIED HIGH. EXACT ORDER CODE QUALIFICATION HOLD. U10 / U11 PIN 4: TRUE NC / INTENTIONAL_NC.
PIN 19: DATASHEET/REFERENCE INTENTIONAL FLOAT MODE 1 COMMUNITY IMPLEMENTATION; TP41 ONLY PIN 10: ROSC_SEL REFERENCE FLOAT / TEST POINT; NO BIAS ADDED PINS 22/23/25/26: UNLOADED TEST OUTPUTS; R27 DNP
0.8V LDO
A1: Bitmain BM1373. Part Number: BM1373. Configuration: Mode 1. Approved pin mapping, Mode strap and RI termination preserved. ENGINEERING DRAFT: power startup, thermal protection and mechanical stack require validation.
Direction Control HIGH= A -> B LOW = A <- B

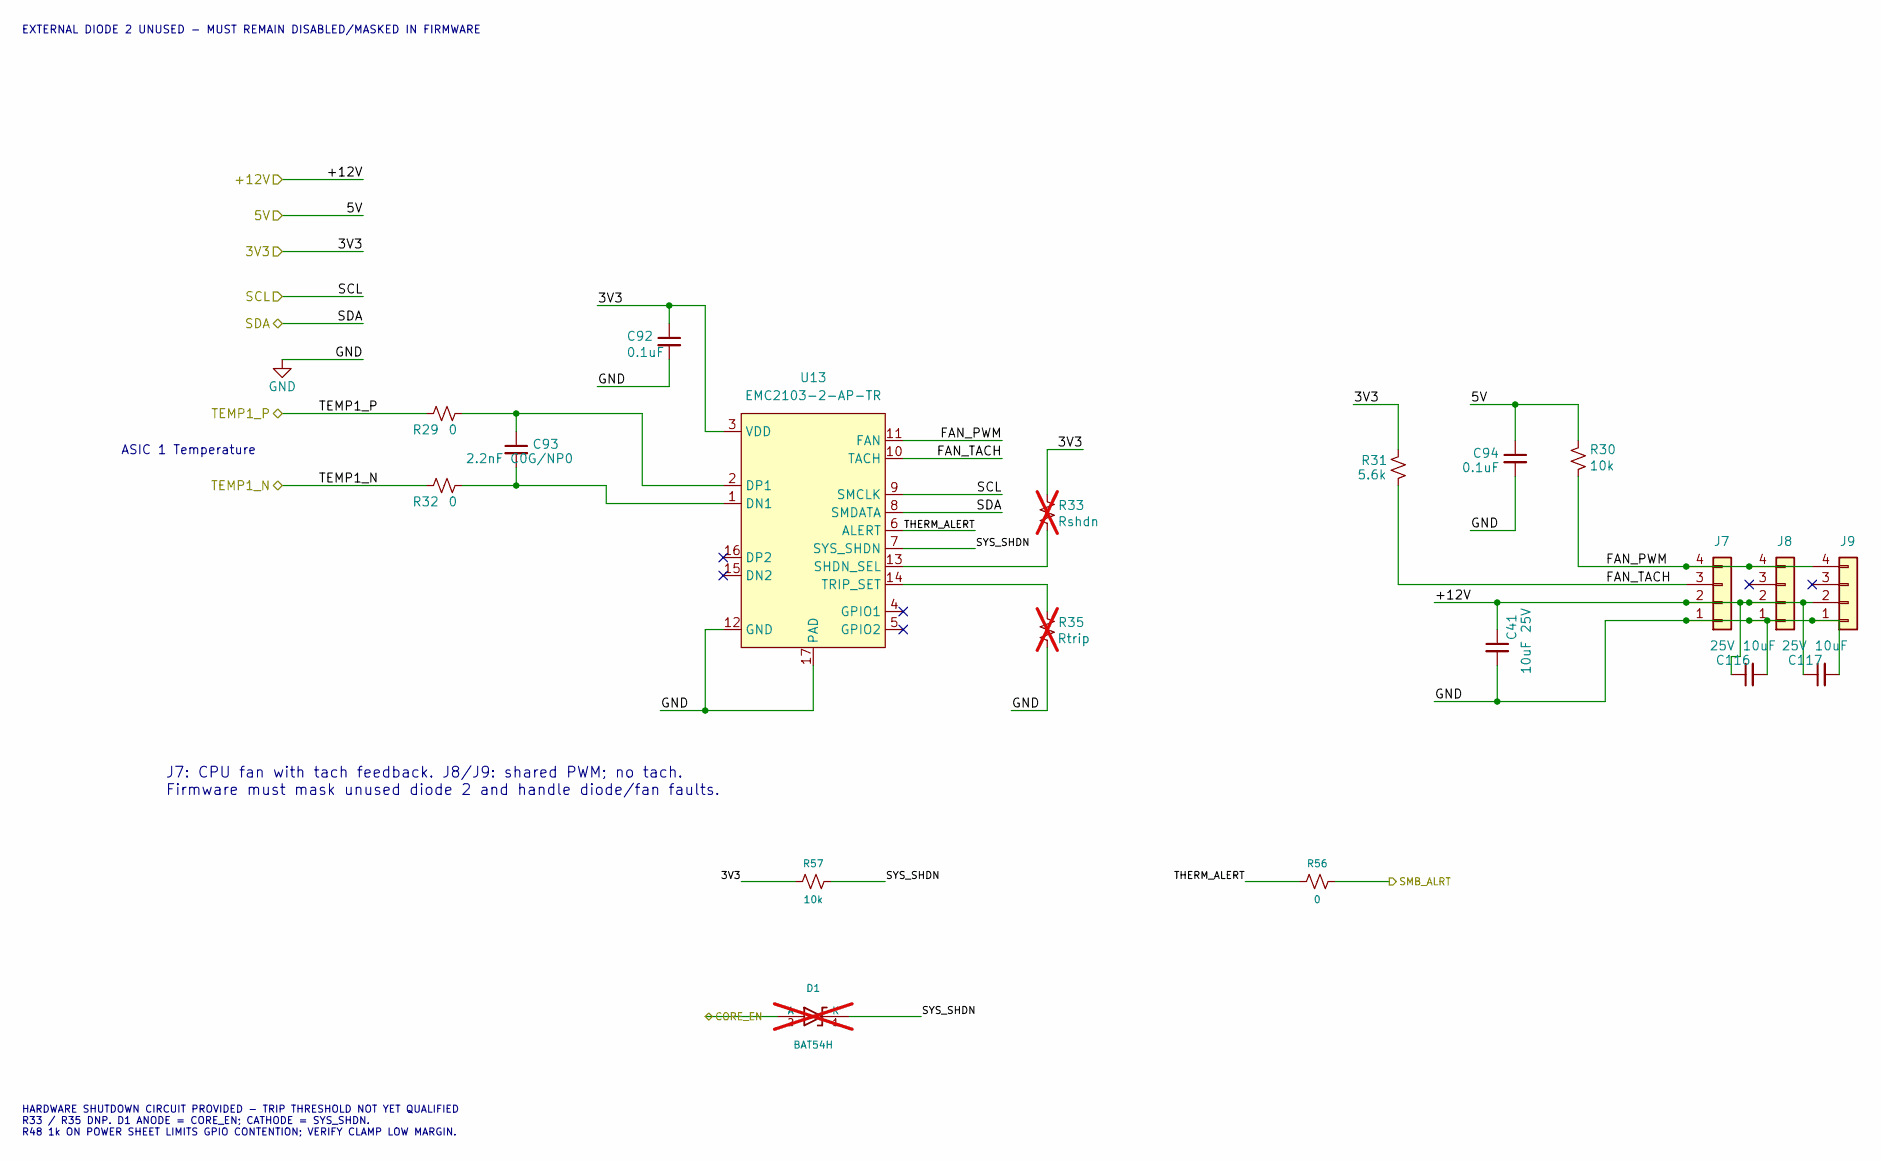
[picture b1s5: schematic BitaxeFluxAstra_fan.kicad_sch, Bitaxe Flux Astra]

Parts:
C41, C116, C117: 10uF; C_0603_1608Metric; Voltage 25V; PARTNO GRM188R61E106KA73D; LCSC C344022
C92, C94: 0.1uF; C_0402_1005Metric; PARTNO KGM05AR71C104KH
C93: 2.2nF C0G/NP0; C_0402_1005Metric; PARTNO TBD / QUALIFY
D1: BAT54H; D_SOD-123F; PARTNO BAT54H,115; not fitted
J7, J8, J9: Conn_01x04; 470531000; PARTNO 0470531000
R29, R32, R56: 0; R_0402_1005Metric; PARTNO RC0402JR-070RL
R30: 10k; R_0402_1005Metric; PARTNO RC0402JR-0710KL; LCSC C25744
R31: 5.6k; R_0402_1005Metric; PARTNO RC0402FR-075K6L
R33: Rshdn; R_0402_1005Metric; PARTNO TBD / QUALIFY; not fitted
R35: Rtrip; R_0402_1005Metric; PARTNO TBD / QUALIFY; not fitted
R57: 10k; R_0402_1005Metric; PARTNO RC0402JR-0710KL
U13: EMC2103-2-AP-TR; QFN-16-1EP_4x4mm_P0.65mm_EP2.1x2.1mm; PARTNO EMC2103-2-AP-TR

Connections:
3V3: C92.1, R31.2, R33.2, R57.1, U13.3 (VDD); also elsewhere on the board
+12V: C41.1, C116.1, C117.1, J7.2, J8.2, J9.2; also elsewhere on the board
/5V: C94.1, R30.2; also elsewhere on the board
/ASIC/TEMP1_N: R32.2; also elsewhere on the board
/ASIC/TEMP1_P: R29.2; also elsewhere on the board
/CORE_EN: D1.2 (A); also elsewhere on the board
/ESP32/SCL: U13.9 (SMCLK); also elsewhere on the board
/ESP32/SDA: U13.8 (SMDATA); also elsewhere on the board
/ESP32/SMB_ALRT: R56.2; also elsewhere on the board
/fan/FAN_PWM: J7.4, J8.4, J9.4, R30.1, U13.11 (FAN)
/fan/FAN_TACH: J7.3, R31.1, U13.10 (TACH)
/fan/SYS_SHDN: D1.1 (K), R57.2, U13.7 (SYS_SHDN)
/fan/THERM_ALERT: R56.1, U13.6 (ALERT)
GND: C41.2, C92.2, C94.2, C116.2, C117.2, J7.1, J8.1, J9.1, R35.1, U13.12 (GND), U13.17 (PAD); also elsewhere on the board
unnamed: C93.2, R32.1, U13.1 (DN1)
unnamed: C93.1, R29.1, U13.2 (DP1)
unnamed: R33.1, U13.13 (SHDN_SEL)
unnamed: R35.2, U13.14 (TRIP_SET)

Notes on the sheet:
J7: CPU fan with tach feedback. J8/J9: shared PWM; no tach. Firmware must mask unused diode 2 and handle diode/fan faults.
EXTERNAL DIODE 2 UNUSED - MUST REMAIN DISABLED/MASKED IN FIRMWARE
ASIC 1 Temperature
HARDWARE SHUTDOWN CIRCUIT PROVIDED - TRIP THRESHOLD NOT YET QUALIFIED R33 / R35 DNP. D1 ANODE = CORE_EN; CATHODE = SYS_SHDN. R48 1k ON POWER SHEET LIMITS GPIO CONTENTION; VERIFY CLAMP LOW MARGIN.

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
